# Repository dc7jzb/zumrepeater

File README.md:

# zumrepeater
Kicad files for the Zum duplex repeater

From a project from Dragan Spiroski Z32IT.
Idea here: https://www.facebook.com/groups/1388328754562371/permalink/1631919806869930/?comment_id=1632624953466082&reply_comment_id=1632626550132589&notif_id=1513960942157026&notif_t=group_comment

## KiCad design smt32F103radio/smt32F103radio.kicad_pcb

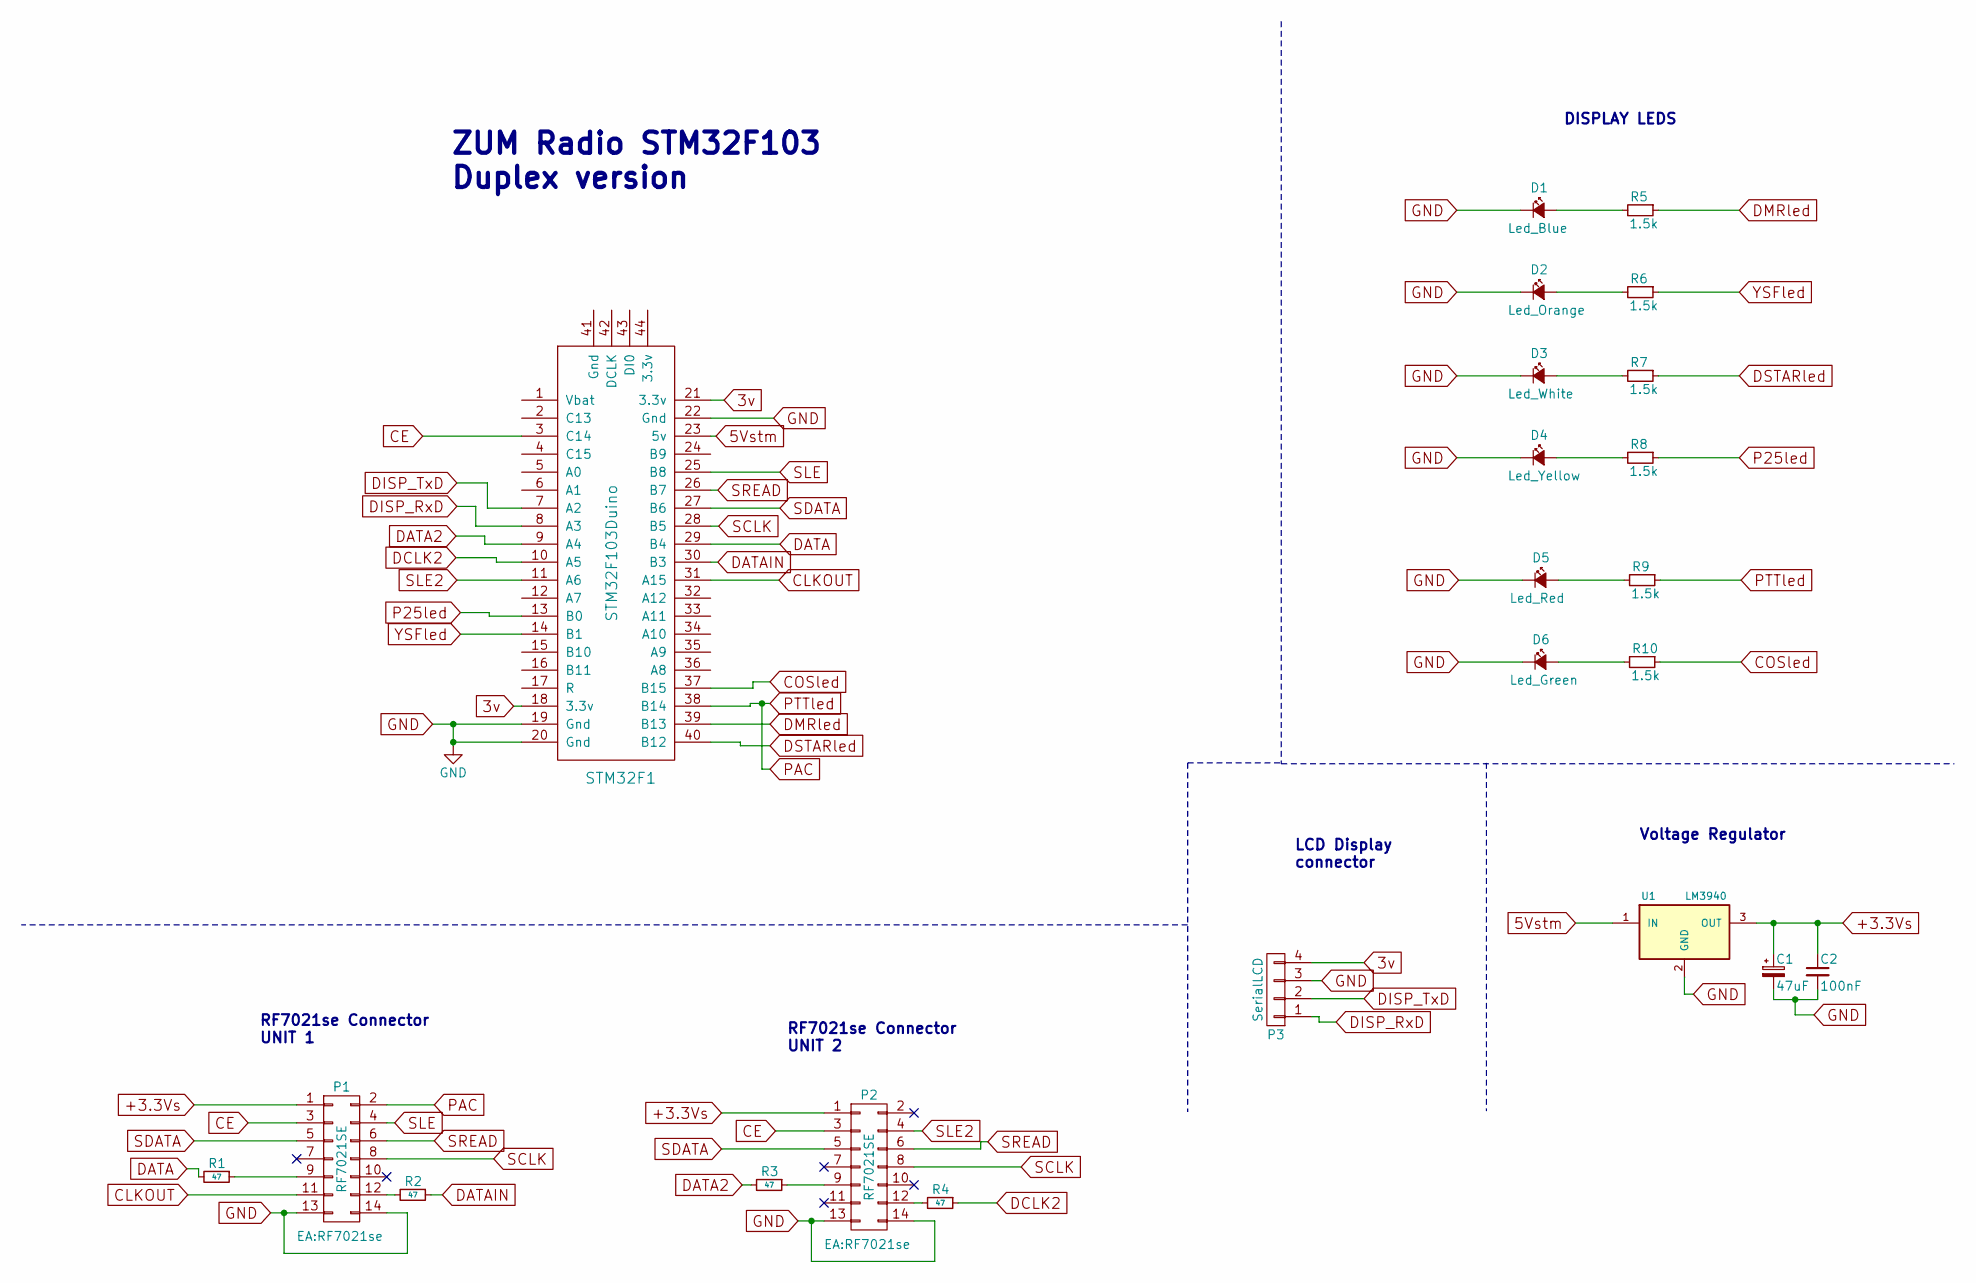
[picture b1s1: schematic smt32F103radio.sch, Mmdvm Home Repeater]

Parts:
C1: 47uF; C_1206_HandSoldering
C2: 100nF; C_1206_HandSoldering
D1: Led_Blue; LED_1206_HandSoldering
D2: Led_Orange; LED_1206_HandSoldering
D3: Led_White; LED_1206_HandSoldering
D4: Led_Yellow; LED_1206_HandSoldering
D5: Led_Red; LED_1206_HandSoldering
D6: Led_Green; LED_1206_HandSoldering
P1, P2: RF7021SE; RF7021se
P3: SerialLCD; Socket_Strip_Straight_1x04_Pitch2.54mm
R1, R2, R3, R4: 47; R_1206_HandSoldering
R5, R6, R7, R8, R9, R10: 1.5k; R_1206_HandSoldering
STM32F1: STM32F103Duino; STM32F103
U1: LM3940; TO-220-3_Horizontal

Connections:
3v: P3.4, STM32F1.18 (3.3v), STM32F1.21 (3.3v)
5Vstm: STM32F1.23 (5v), U1.1 (IN)
+3.3Vs: C1.1, C2.1, P1.1 (3V3), P2.1 (3V3), U1.3 (OUT)
CE: P1.3 (OE), P2.3 (OE), STM32F1.3 (C14)
CLKOUT: P1.11 (CLKOUT), STM32F1.31 (A15)
COSled: R10.1, STM32F1.37 (B15)
DATA: R1.2, STM32F1.29 (B4)
DATA2: R3.2, STM32F1.9 (A4)
DATAIN: R2.1, STM32F1.30 (B3)
DCLK2: R4.1, STM32F1.10 (A5)
DISP_RxD: P3.1, STM32F1.8 (A3)
DISP_TxD: P3.2, STM32F1.7 (A2)
DMRled: R5.1, STM32F1.39 (B13)
DSTARled: R7.1, STM32F1.40 (B12)
GND: C1.2, C2.2, D1.1 (K), D2.1 (K), D3.1 (K), D4.1 (K), D5.1 (K), D6.1 (K), P1.13 (GND), P1.14 (GND), P2.13 (GND), P2.14 (GND), P3.3, STM32F1.19 (Gnd), STM32F1.20 (Gnd), STM32F1.22 (Gnd), U1.2 (GND)
unnamed: D1.2 (A), R5.2
unnamed: D2.2 (A), R6.2
unnamed: D3.2 (A), R7.2
unnamed: D4.2 (A), R8.2
unnamed: D5.2 (A), R9.2
unnamed: D6.2 (A), R10.2
unnamed: P1.9 (DATAOUT), R1.1
unnamed: P1.12 (DATAIN), R2.2
unnamed: P2.9 (DATAOUT), R3.1
unnamed: P2.12 (DATAIN), R4.2
P25led: R8.1, STM32F1.13 (B0)
PAC: P1.2, R9.1, STM32F1.38 (B14)
SCLK: P1.8 (SCLK), P2.8 (SCLK), STM32F1.28 (B5)
SDATA: P1.5 (SDATA), P2.5 (SDATA), STM32F1.27 (B6)
SLE: P1.4 (SLE), STM32F1.25 (B8)
SLE2: P2.4 (SLE), STM32F1.11 (A6)
SREAD: P1.6 (SREAD), P2.6 (SREAD), STM32F1.26 (B7)
YSFled: R6.1, STM32F1.14 (B1)

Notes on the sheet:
DISPLAY LEDS
RF7021se Connector UNIT 1
RF7021se Connector UNIT 2
Voltage Regulator
ZUM Radio STM32F103 Duplex version
LCD Display connector

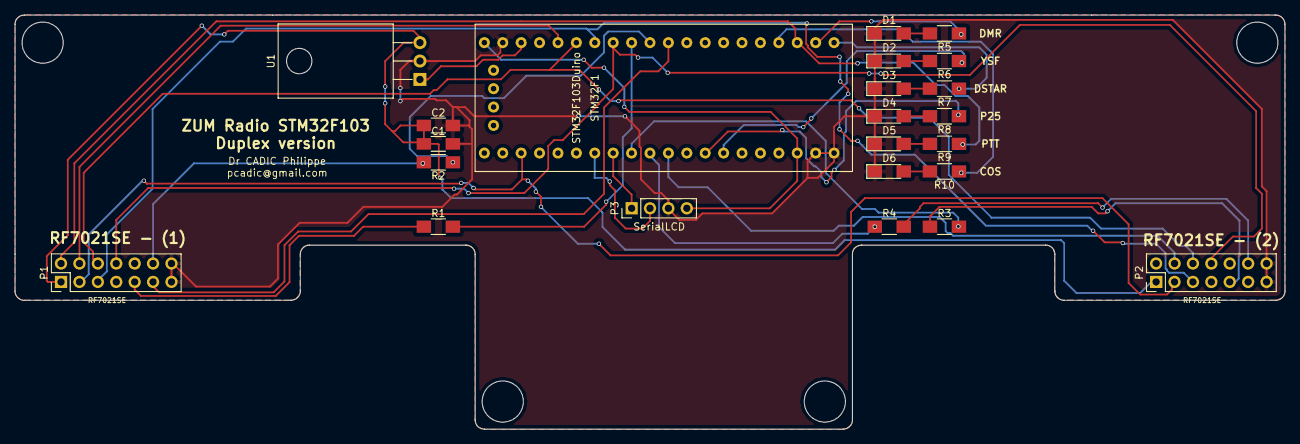
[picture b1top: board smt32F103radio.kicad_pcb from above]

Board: 2 copper layers, 175.3 x 57.2 mm, 23 parts (0 on the bottom side), 33 nets.
